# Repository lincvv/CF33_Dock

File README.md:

# CF33_Dock
**Detect Bypass Station for Panasonic CF33 with 4 USB Ports**

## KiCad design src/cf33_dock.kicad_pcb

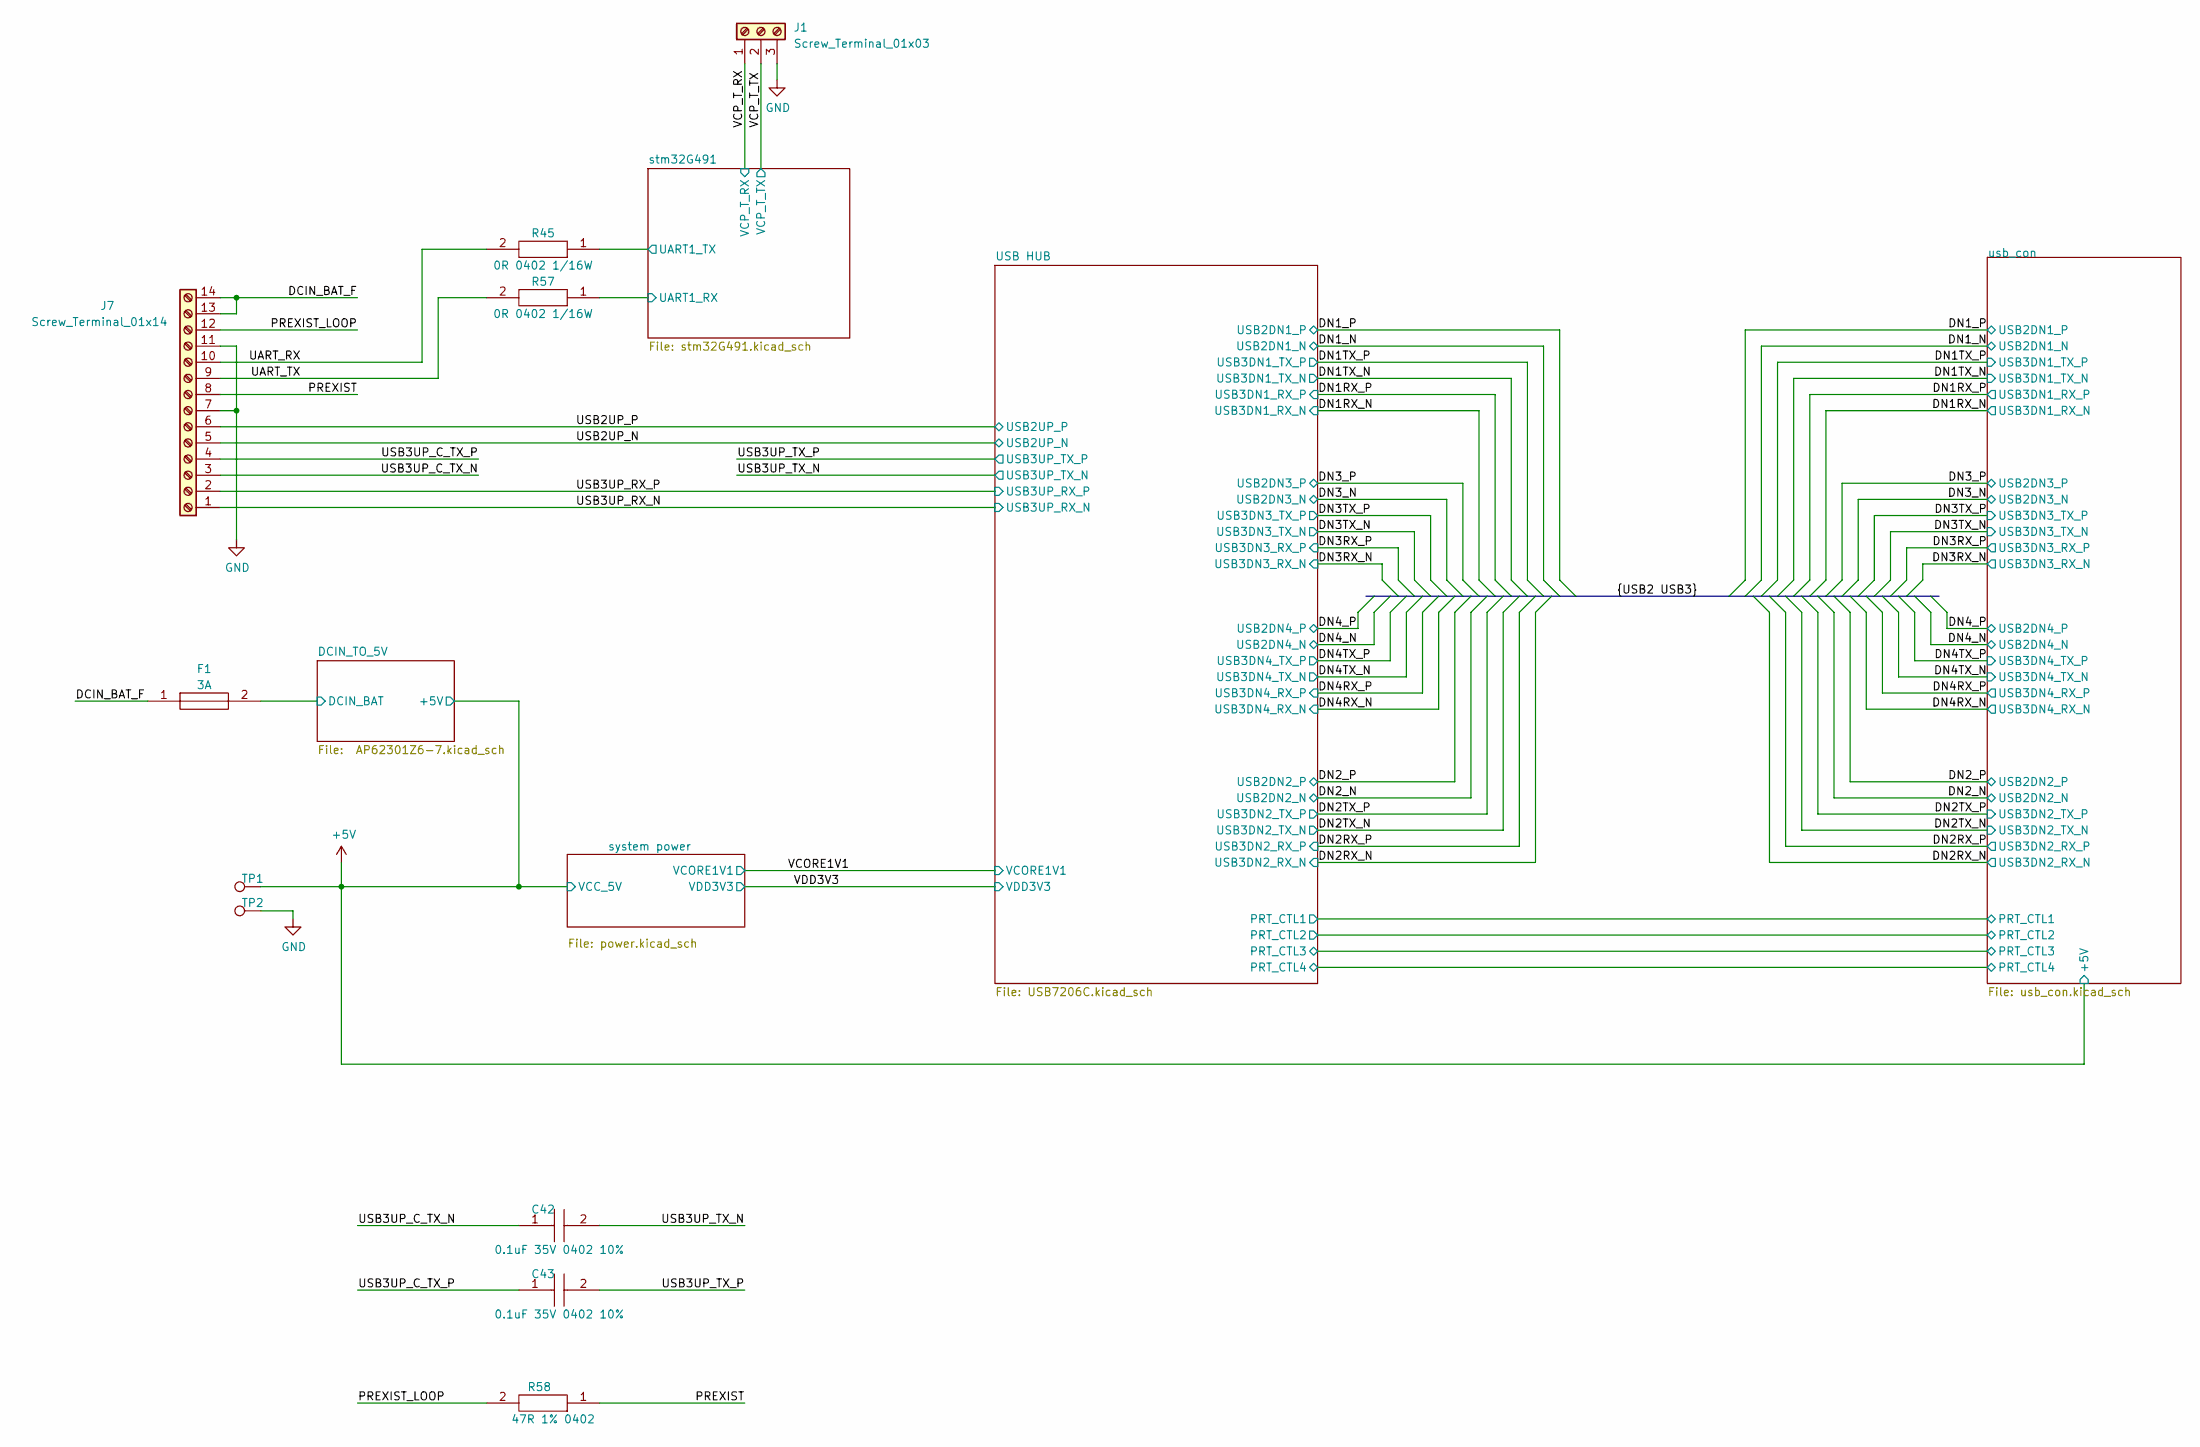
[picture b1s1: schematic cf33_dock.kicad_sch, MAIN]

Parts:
C42, C43: 0.1uF 35V 0402 10%; C_0402_1005Metric; Manufacturer_Part_Number CGA2B3X7R1V104K050BB; Mouser Part Number 810-CGA2B3X7R1V104K
F1: 3A; SF1206F300M2; Manufacturer_Part_Number SF-1206F300M-2
J1: Screw_Terminal_01x03; PinHeader_1x03_P2.54mm_Vertical
J7: Screw_Terminal_01x14; PinHeader_1x14_P2.54mm_Vertical
R45, R57: 0R 0402 1/16W; R_0402_1005Metric; Manufacturer_Part_Number CRCW04020000ZSTD; Mouser Part Number 71-CRCW0402-0
R58: 47R 1% 0402; R_0402_1005Metric; Manufacturer_Part_Number CR0402-FX-47R0GLF
TP1, TP2: TestPoint; TestPoint_THTPad_D2.0mm_Drill1.0mm

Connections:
+5V: TP1.1; also elsewhere on the board
/DCIN_BAT_F: F1.1, J7.13, J7.14
/PREXIST: J7.8, R58.1
/PREXIST_LOOP: J7.12, R58.2
/UART_RX: J7.10, R45.2
/UART_TX: J7.9, R57.2
/USB2UP_N: J7.5; also elsewhere on the board
/USB2UP_P: J7.6; also elsewhere on the board
/USB3UP_C_TX_N: C42.1, J7.3
/USB3UP_C_TX_P: C43.1, J7.4
/USB3UP_RX_N: J7.1; also elsewhere on the board
/USB3UP_RX_P: J7.2; also elsewhere on the board
/USB3UP_TX_N: C42.2; also elsewhere on the board
/USB3UP_TX_P: C43.2; also elsewhere on the board
/VCP_T_RX: J1.1; also elsewhere on the board
/VCP_T_TX: J1.2; also elsewhere on the board
/stm32G491/UART1_RX: R57.1; also elsewhere on the board
/stm32G491/UART1_TX: R45.1; also elsewhere on the board
DCIN_BAT: F1.2; also elsewhere on the board
GND: J1.3, J7.7, J7.11, TP2.1; also elsewhere on the board

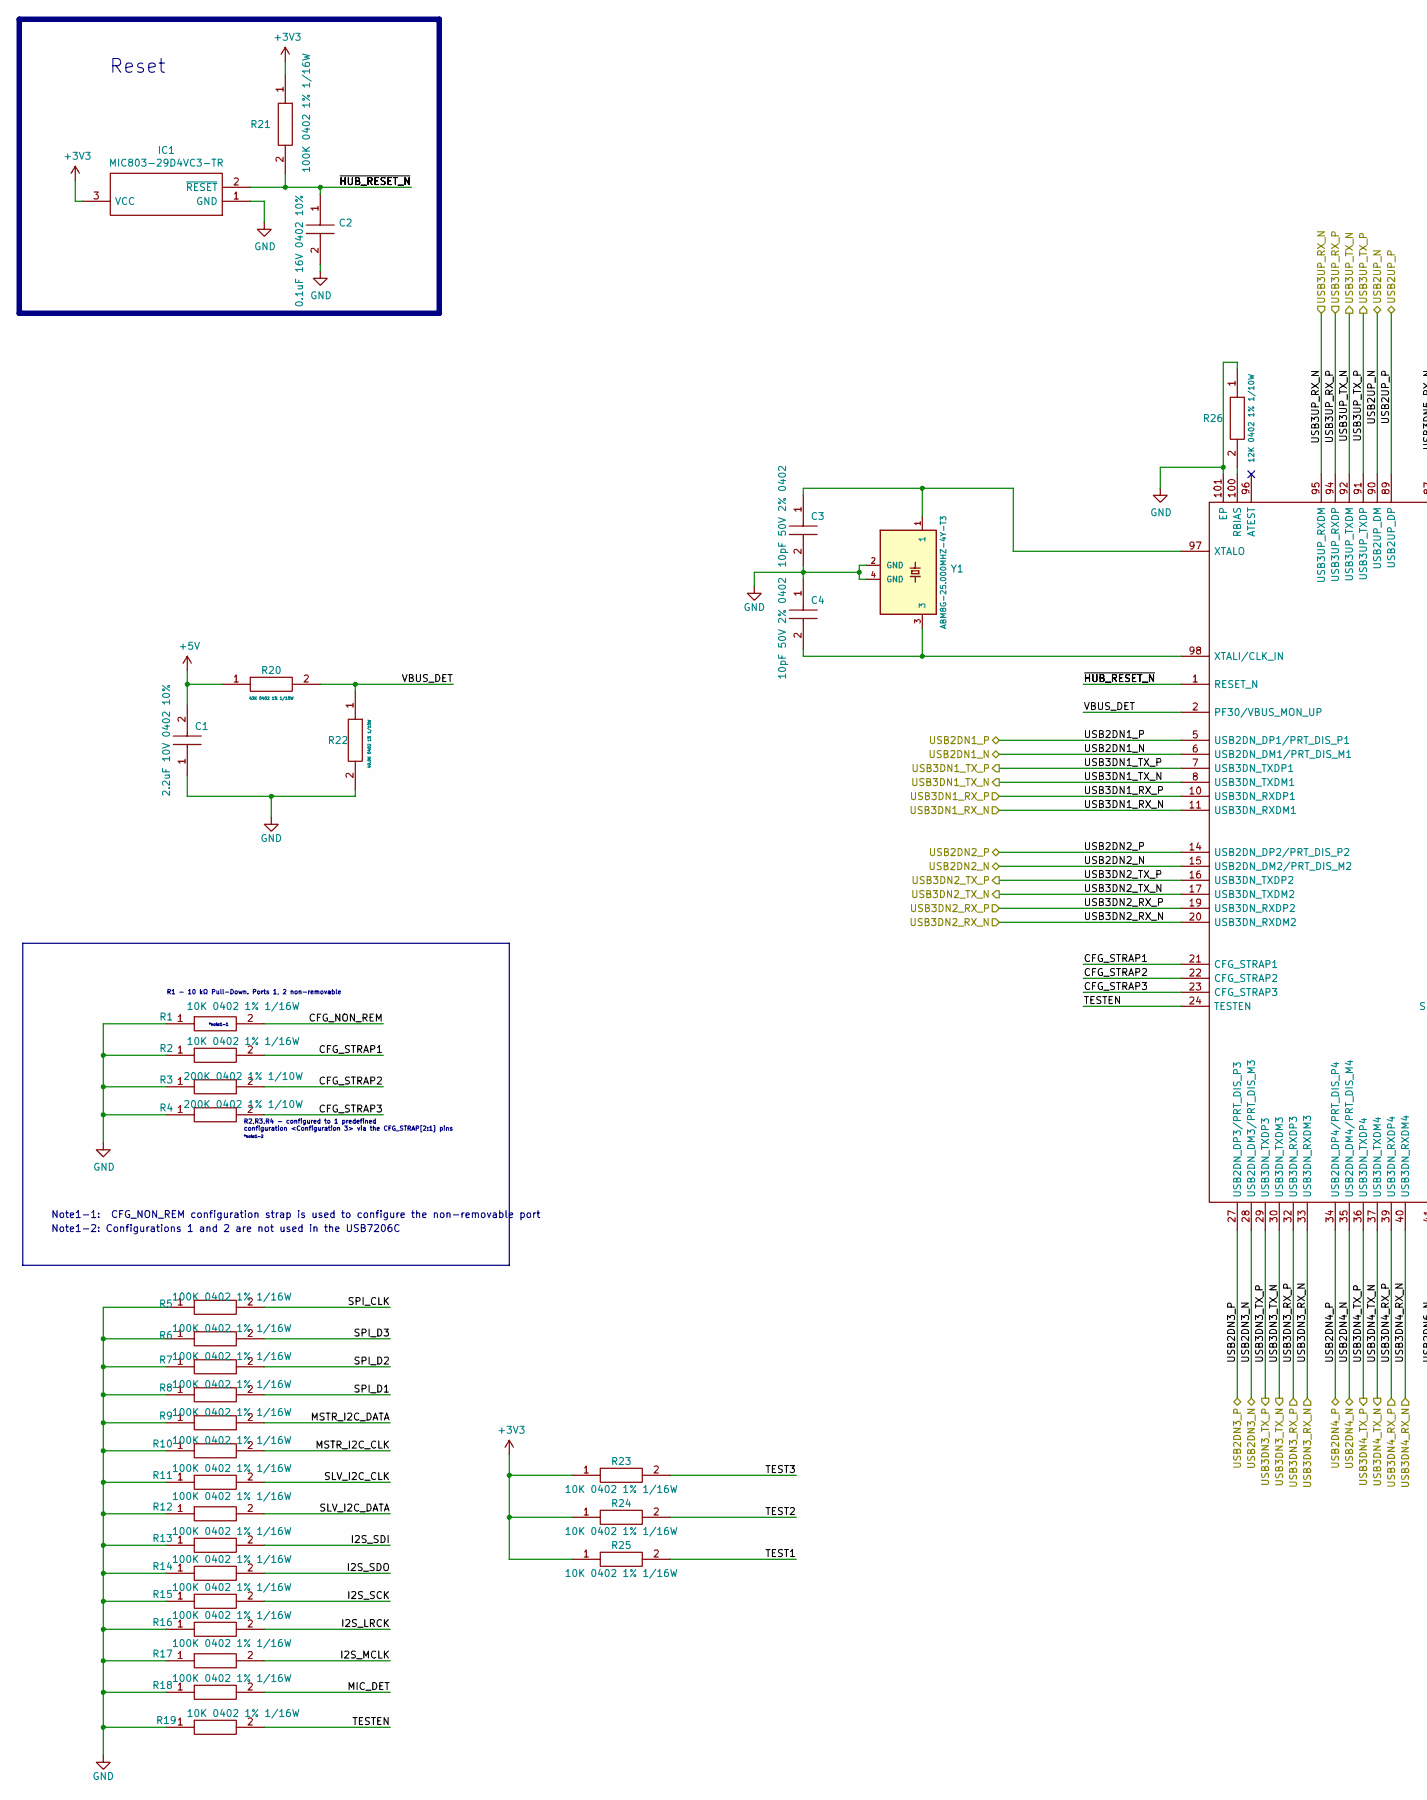
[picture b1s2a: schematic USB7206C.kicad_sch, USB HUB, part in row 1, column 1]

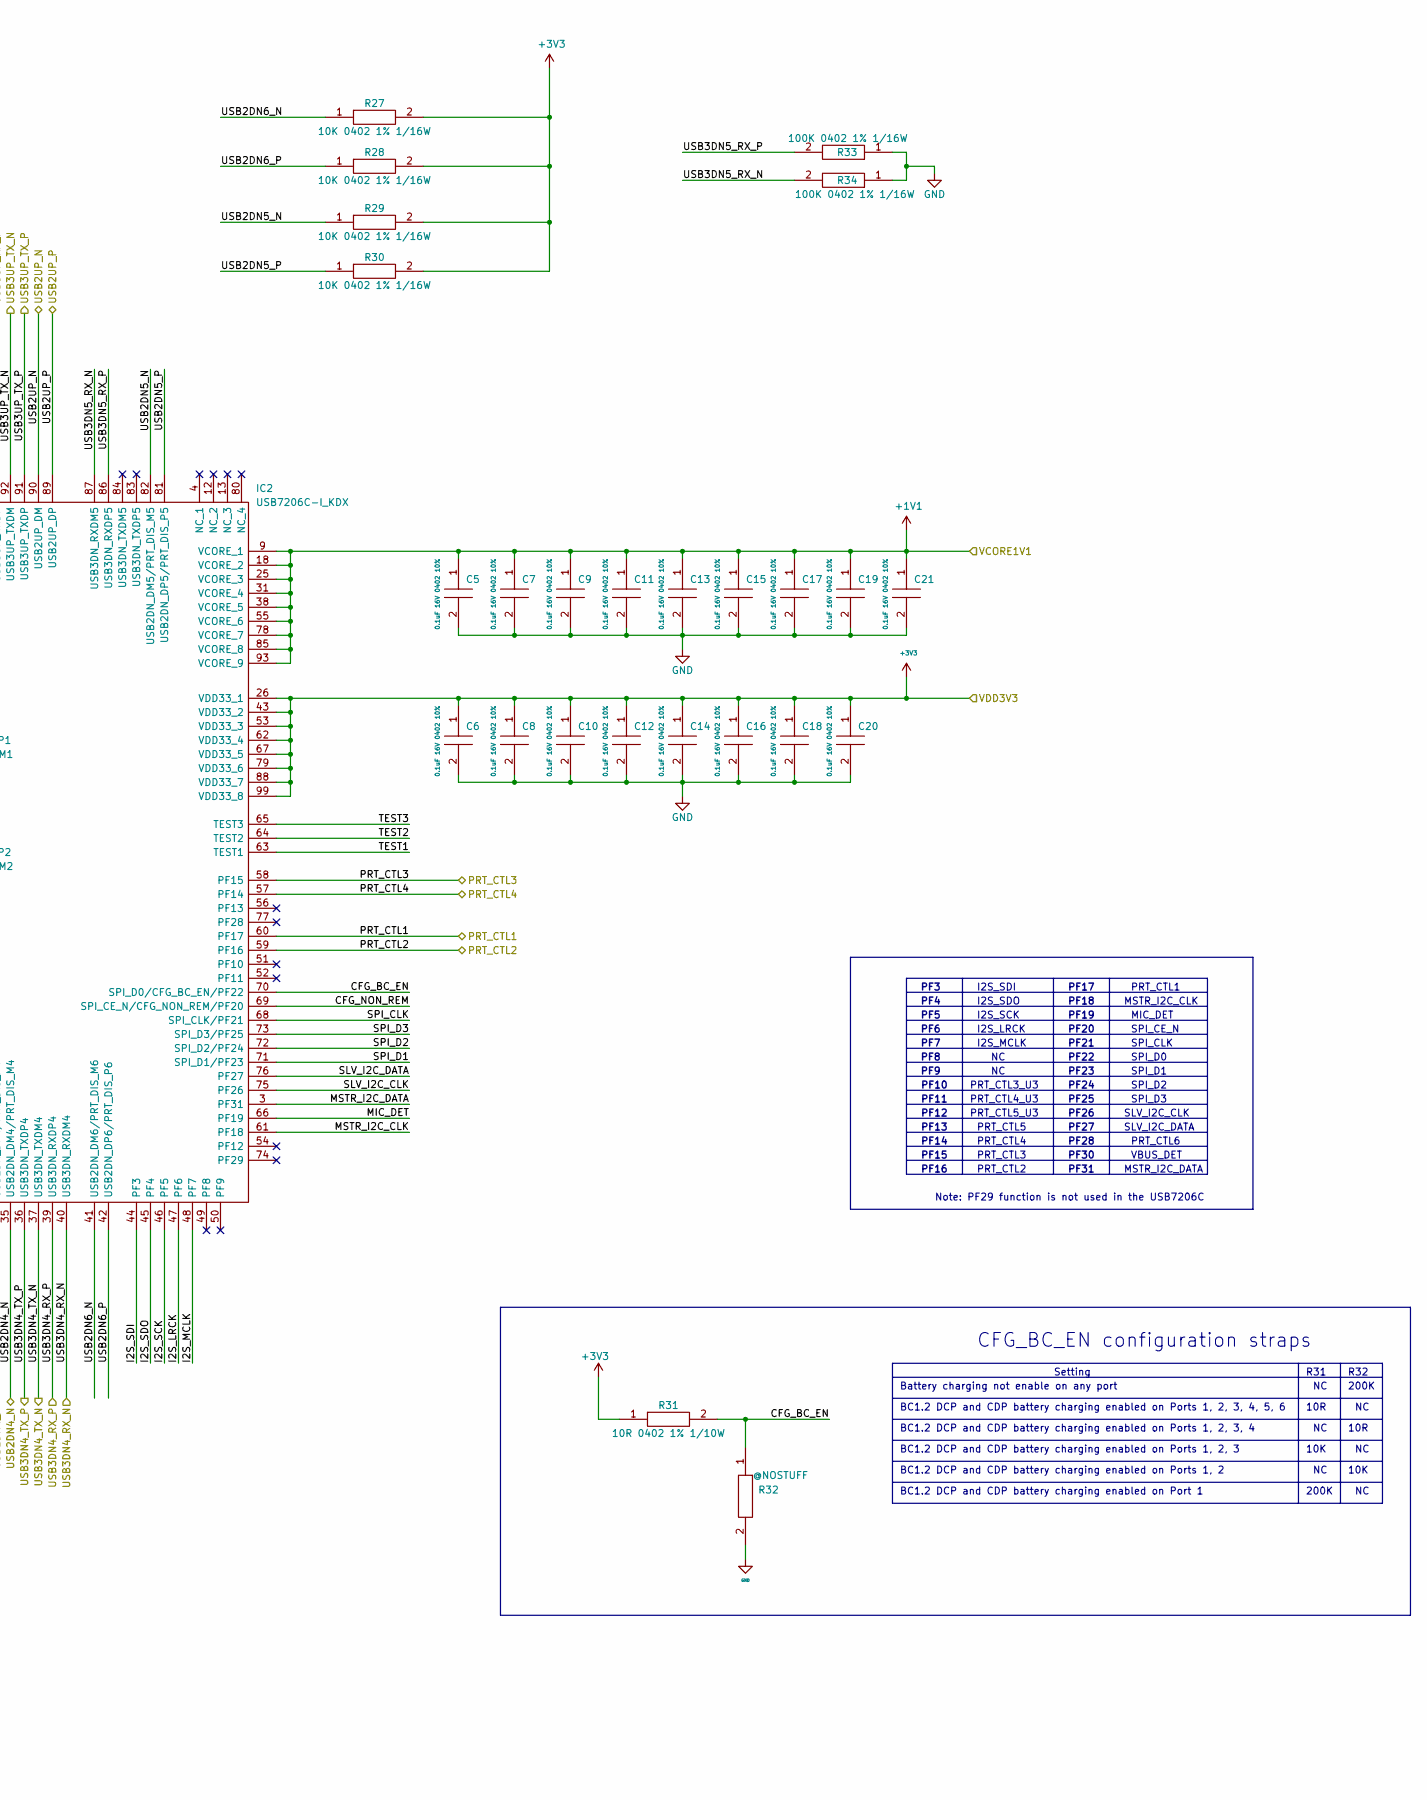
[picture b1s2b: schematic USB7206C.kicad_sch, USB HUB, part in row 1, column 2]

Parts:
C1: 2.2uF 10V 0402 10%; C_0402_1005Metric; Manufacturer_Part_Number GRM155C71A225KE11D; Mouser Part Number 81-GRM155C71A225KE1D
C2, C5, C6, C7, C8, C9, C10, C11, C12, C13, C14, C15, C16, C17, C18, C19, C20, C21: 0.1uF 16V 0402 10%; C_0402_1005Metric; Manufacturer_Part_Number GRM155R71C104KA88D; Mouser Part Number N/A
C3, C4: 10pF 50V 2% 0402; C_0402_1005Metric; Manufacturer_Part_Number GJM1555C1H100GB01D; Mouser Part Number 81-GJM1555C1H100GB01
IC1: MIC803-29D4VC3-TR; SOT65P210X100-3N; Manufacturer_Part_Number MIC803-29D4VC3-TR; Mouser Part Number 998-MIC803-29D4VC3TR
IC2: USB7206C-I_KDX; QFN40P1200X1200X90-101N-D; Mouser Part Number 579-USB7206C-I/KDX
R1, R2, R19, R23, R24, R25, R27, R28, R29, R30: 10K 0402 1% 1/16W; R_0402_1005Metric; Manufacturer_Part_Number AC0402FR-0710KL; Mouser Part Number 603-AC0402FR-0710KL
R3, R4: 200K 0402 1% 1/10W; R_0402_1005Metric; Manufacturer_Part_Number ERJ-U02F2003X
R5, R6, R7, R8, R9, R10, R11, R12, R13, R14, R15, R16, R17, R18, R21, R33, R34: 100K 0402 1% 1/16W; R_0402_1005Metric; Manufacturer_Part_Number SFR01MZPF1003; Mouser Part Number 755-SFR01MZPF1003
R20: 43K 0402 1% 1/10W; R_0402_1005Metric; Manufacturer_Part_Number ERJ-U02F4302X; Mouser Part Number 667-ERJ-U02F4302X
R22: 49.9K 0402 1% 1/10W; R_0402_1005Metric; Manufacturer_Part_Number ERJ-U02F4992X; Mouser Part Number 667-ERJ-U02F4992X
R26: 12K 0402 1% 1/10W; R_0402_1005Metric; Manufacturer_Part_Number ERJ-U02F1202X
R31, R32: 10R 0402 1% 1/10W; R_0402_1005Metric; Manufacturer_Part_Number ERJ-2RKF10R0X; Mouser Part Number 667-ERJ-2RKF10R0X
Y1: ABM8G-25.000MHZ-4Y-T3; ABM8G48000MHZ18D2YT; Manufacturer_Part_Number ABM8G-25.000MHZ-4Y-T3; Mouser Part Number 815-ABM8G-25-4YT3

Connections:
+1V1: C5.1, C7.1, C9.1, C11.1, C13.1, C15.1, C17.1, C19.1, C21.1, IC2.9 (VCORE_1), IC2.18 (VCORE_2), IC2.25 (VCORE_3), IC2.31 (VCORE_4), IC2.38 (VCORE_5), IC2.55 (VCORE_6), IC2.78 (VCORE_7), IC2.85 (VCORE_8), IC2.93 (VCORE_9); also elsewhere on the board
+3V3: C6.1, C8.1, C10.1, C12.1, C14.1, C16.1, C18.1, C20.1, IC1.3 (VCC), IC2.26 (VDD33_1), IC2.43 (VDD33_2), IC2.53 (VDD33_3), IC2.62 (VDD33_4), IC2.67 (VDD33_5), IC2.79 (VDD33_6), IC2.88 (VDD33_7), IC2.99 (VDD33_8), R21.1, R23.1, R24.1, R25.1, R27.2, R28.2, R29.2, R30.2, R31.1; also elsewhere on the board
+5V: C1.2, R20.1; also elsewhere on the board
/DN1RX_N: IC2.11 (USB3DN_RXDM1); also elsewhere on the board
/DN1RX_P: IC2.10 (USB3DN_RXDP1); also elsewhere on the board
/DN1TX_N: IC2.8 (USB3DN_TXDM1); also elsewhere on the board
/DN1TX_P: IC2.7 (USB3DN_TXDP1); also elsewhere on the board
/DN1_N: IC2.6 (USB2DN_DM1/PRT_DIS_M1); also elsewhere on the board
/DN1_P: IC2.5 (USB2DN_DP1/PRT_DIS_P1); also elsewhere on the board
/DN2RX_N: IC2.20 (USB3DN_RXDM2); also elsewhere on the board
/DN2RX_P: IC2.19 (USB3DN_RXDP2); also elsewhere on the board
/DN2TX_N: IC2.17 (USB3DN_TXDM2); also elsewhere on the board
/DN2TX_P: IC2.16 (USB3DN_TXDP2); also elsewhere on the board
/DN2_N: IC2.15 (USB2DN_DM2/PRT_DIS_M2); also elsewhere on the board
/DN2_P: IC2.14 (USB2DN_DP2/PRT_DIS_P2); also elsewhere on the board
/DN3RX_N: IC2.33 (USB3DN_RXDM3); also elsewhere on the board
/DN3RX_P: IC2.32 (USB3DN_RXDP3); also elsewhere on the board
/DN3TX_N: IC2.30 (USB3DN_TXDM3); also elsewhere on the board
/DN3TX_P: IC2.29 (USB3DN_TXDP3); also elsewhere on the board
/DN3_N: IC2.28 (USB2DN_DM3/PRT_DIS_M3); also elsewhere on the board
/DN3_P: IC2.27 (USB2DN_DP3/PRT_DIS_P3); also elsewhere on the board
/DN4RX_N: IC2.40 (USB3DN_RXDM4); also elsewhere on the board
/DN4RX_P: IC2.39 (USB3DN_RXDP4); also elsewhere on the board
/DN4TX_N: IC2.37 (USB3DN_TXDM4); also elsewhere on the board
/DN4TX_P: IC2.36 (USB3DN_TXDP4); also elsewhere on the board
/DN4_N: IC2.35 (USB2DN_DM4/PRT_DIS_M4); also elsewhere on the board
/DN4_P: IC2.34 (USB2DN_DP4/PRT_DIS_P4); also elsewhere on the board
/USB2UP_N: IC2.90 (USB2UP_DM); also elsewhere on the board
/USB2UP_P: IC2.89 (USB2UP_DP); also elsewhere on the board
/USB3UP_RX_N: IC2.95 (USB3UP_RXDM); also elsewhere on the board
/USB3UP_RX_P: IC2.94 (USB3UP_RXDP); also elsewhere on the board
/USB3UP_TX_N: IC2.92 (USB3UP_TXDM); also elsewhere on the board
/USB3UP_TX_P: IC2.91 (USB3UP_TXDP); also elsewhere on the board
/USB HUB/CFG_BC_EN: IC2.70 (SPI_D0/CFG_BC_EN/PF22), R31.2, R32.1
/USB HUB/CFG_NON_REM: IC2.69 (SPI_CE_N/CFG_NON_REM/PF20), R1.2
/USB HUB/CFG_STRAP1: IC2.21 (CFG_STRAP1), R2.2
/USB HUB/CFG_STRAP2: IC2.22 (CFG_STRAP2), R3.2
/USB HUB/CFG_STRAP3: IC2.23 (CFG_STRAP3), R4.2
/USB HUB/HUB_RESET_N: C2.1, IC1.2 (~RESET), IC2.1 (RESET_N), R21.2
/USB HUB/I2S_LRCK: IC2.47 (PF6), R16.2
/USB HUB/I2S_MCLK: IC2.48 (PF7), R17.2
/USB HUB/I2S_SCK: IC2.46 (PF5), R15.2
/USB HUB/I2S_SDI: IC2.44 (PF3), R13.2
/USB HUB/I2S_SDO: IC2.45 (PF4), R14.2
/USB HUB/MIC_DET: IC2.66 (PF19), R18.2
/USB HUB/MSTR_I2C_CLK: IC2.61 (PF18), R10.2
/USB HUB/MSTR_I2C_DATA: IC2.3 (PF31), R9.2
/USB HUB/PRT_CTL1: IC2.60 (PF17); also elsewhere on the board
/USB HUB/PRT_CTL2: IC2.59 (PF16); also elsewhere on the board
/USB HUB/PRT_CTL3: IC2.58 (PF15); also elsewhere on the board
/USB HUB/PRT_CTL4: IC2.57 (PF14); also elsewhere on the board
/USB HUB/SLV_I2C_CLK: IC2.75 (PF26), R11.2
/USB HUB/SLV_I2C_DATA: IC2.76 (PF27), R12.2
/USB HUB/SPI_CLK: IC2.68 (SPI_CLK/PF21), R5.2
/USB HUB/SPI_D1: IC2.71 (SPI_D1/PF23), R8.2
/USB HUB/SPI_D2: IC2.72 (SPI_D2/PF24), R7.2
/USB HUB/SPI_D3: IC2.73 (SPI_D3/PF25), R6.2
/USB HUB/TEST1: IC2.63 (TEST1), R25.2
/USB HUB/TEST2: IC2.64 (TEST2), R24.2
/USB HUB/TEST3: IC2.65 (TEST3), R23.2
/USB HUB/TESTEN: IC2.24 (TESTEN), R19.2
/USB HUB/USB2DN5_N: IC2.82 (USB2DN_DM5/PRT_DIS_M5), R29.1
/USB HUB/USB2DN5_P: IC2.81 (USB2DN_DP5/PRT_DIS_P5), R30.1
/USB HUB/USB2DN6_N: IC2.41 (USB2DN_DM6/PRT_DIS_M6), R27.1
/USB HUB/USB2DN6_P: IC2.42 (USB2DN_DP6/PRT_DIS_P6), R28.1
/USB HUB/USB3DN5_RX_N: IC2.87 (USB3DN_RXDM5), R34.2
/USB HUB/USB3DN5_RX_P: IC2.86 (USB3DN_RXDP5), R33.2
/USB HUB/VBUS_DET: IC2.2 (PF30/VBUS_MON_UP), R20.2, R22.1
GND: C1.1, C2.2, C3.2, C4.1, C5.2, C6.2, C7.2, C8.2, C9.2, C10.2, C11.2, C12.2, C13.2, C14.2, C15.2, C16.2, C17.2, C18.2, C19.2, C20.2, C21.2, IC1.1 (GND), IC2.101 (EP), R1.1, R2.1, R3.1, R4.1, R5.1, R6.1, R7.1, R8.1, R9.1, R10.1, R11.1, R12.1, R13.1, R14.1, R15.1, R16.1, R17.1, R18.1, R19.1, R22.2, R26.1, R32.2, R33.1, R34.1, Y1.2 (GND), Y1.4 (GND); also elsewhere on the board
unnamed: IC2.100 (RBIAS), R26.2
unnamed: C4.2, IC2.98 (XTALI/CLK_IN), Y1.3
unnamed: C3.1, IC2.97 (XTALO), Y1.1

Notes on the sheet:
Reset
10K
MSTR_I2C_CLK
PF17
PF4
PF8
PRT_CTL3
PF5
PF22
Setting
PF10
PRT_CTL3_U3
PF3
PF11
200K
PF13
PF27
PF28
MIC_DET
PF30
PF23
PF15
PRT_CTL6
PF24
BC1.2 DCP and CDP battery charging enabled on Port 1
PF19
PF26
SPI_CE_N
BC1.2 DCP and CDP battery charging enabled on Ports 1, 2, 3
PF20
BC1.2 DCP and CDP battery charging enabled on Ports 1, 2, 3, 4
R31
PF12
Note1-2: Configurations 1 and 2 are not used in the USB7206C
PRT_CTL5_U3
*note1-1
I2S_LRCK
SLV_I2C_CLK
SPI_CLK
Note: PF29 function is not used in the USB7206C

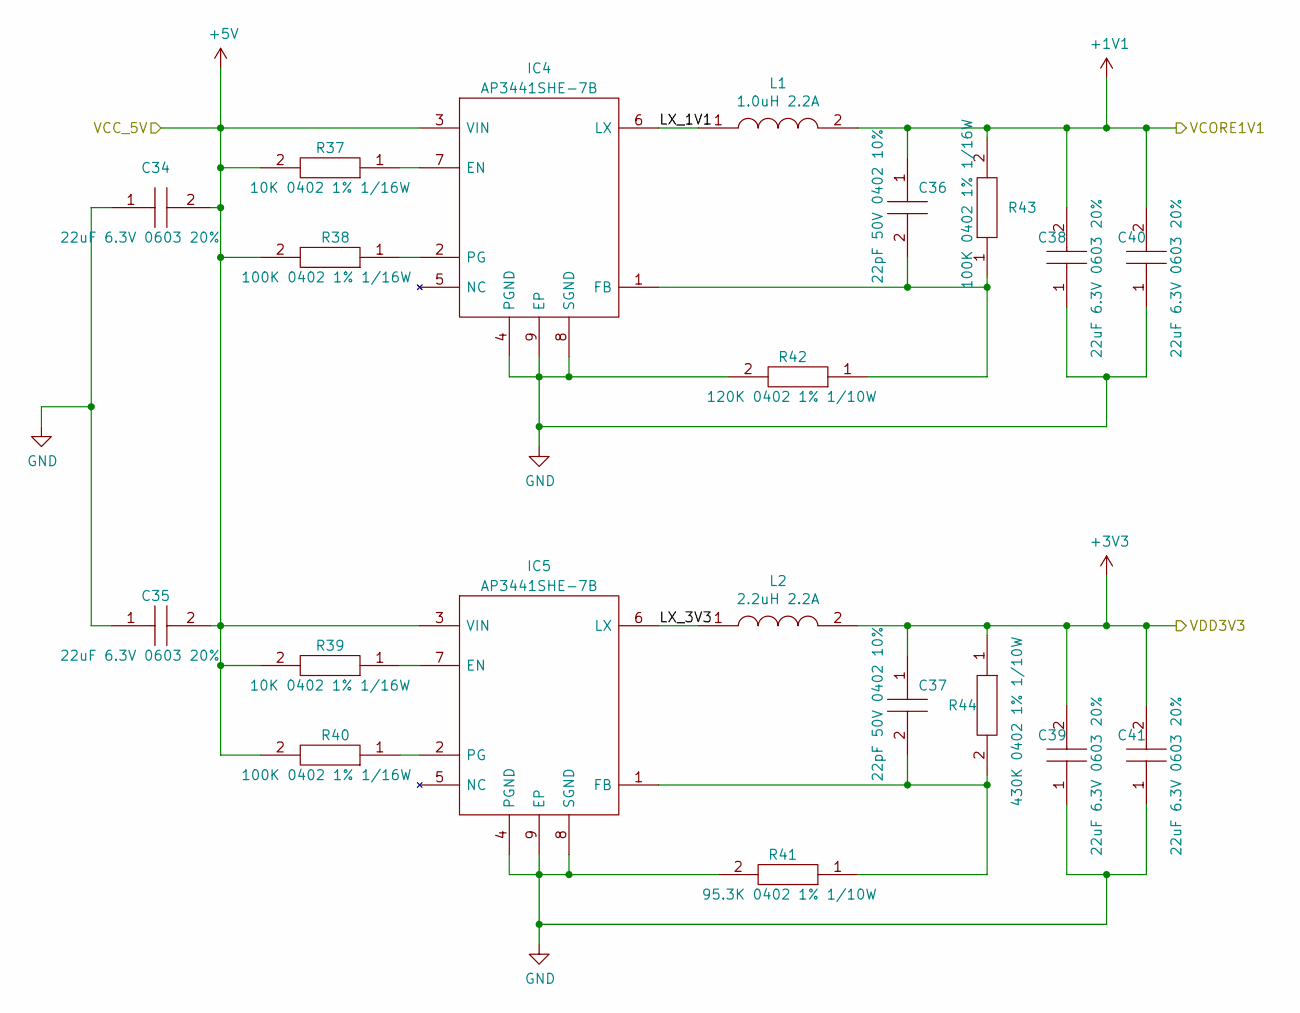
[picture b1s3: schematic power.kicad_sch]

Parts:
C34, C35, C38, C39, C40, C41: 22uF 6.3V 0603 20%; C_0603_1608Metric; Manufacturer_Part_Number GRM188R60J226MEA0D; Mouser Part Number 81-GRM188R60J226ME0D
C36, C37: 22pF 50V 0402 10%; C_0402_1005Metric; Manufacturer_Part_Number C0402C220K5RACTU; Mouser Part Number 80-C0402C220K5RACTU
IC4, IC5: AP3441SHE-7B; SON50P201X201X60-9N-D; Manufacturer_Part_Number AP3441SHE-7B; Mouser Part Number 621-AP3441SHE-7B
L1: 1.0uH 2.2A; 1285ASH1R0MP2; Manufacturer_Part_Number 1285AS-H-1R0M=P2; Mouser Part Number 81-1285AS-H-1R0MP2
L2: 2.2uH 2.2A; DFE2HCAH1R0MJ0L; Manufacturer_Part_Number 1239AS-H-2R2M=P2; Mouser Part Number 81-1239AS-H-2R2MP2
R37, R39: 10K 0402 1% 1/16W; R_0402_1005Metric; Manufacturer_Part_Number AC0402FR-0710KL; Mouser Part Number 603-AC0402FR-0710KL
R38, R40, R43: 100K 0402 1% 1/16W; R_0402_1005Metric; Manufacturer_Part_Number SFR01MZPF1003; Mouser Part Number 755-SFR01MZPF1003
R41: 95.3K 0402 1% 1/10W; R_0402_1005Metric; Manufacturer_Part_Number ERJ-U02F9532X; Mouser Part Number 667-ERJ-U02F9532X
R42: 120K 0402 1% 1/10W; R_0402_1005Metric; Manufacturer_Part_Number ERJ2RKF1203X
R44: 430K 0402 1% 1/10W; R_0402_1005Metric; Manufacturer_Part_Number ERJ-U02F4303X

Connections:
+1V1: C36.1, C38.2, C40.2, L1.2, R43.2; also elsewhere on the board
+3V3: C37.1, C39.2, C41.2, L2.2, R44.1; also elsewhere on the board
+5V: C34.2, C35.2, IC4.3 (VIN), IC5.3 (VIN), R37.2, R38.2, R39.2, R40.2; also elsewhere on the board
/system power/LX_1V1: IC4.6 (LX), L1.1
/system power/LX_3V3: IC5.6 (LX), L2.1
GND: C34.1, C35.1, C38.1, C39.1, C40.1, C41.1, IC4.4 (PGND), IC4.8 (SGND), IC4.9 (EP), IC5.4 (PGND), IC5.8 (SGND), IC5.9 (EP), R41.2, R42.2; also elsewhere on the board
unnamed: IC4.7 (EN), R37.1
unnamed: C36.2, IC4.1 (FB), R42.1, R43.1
unnamed: IC4.2 (PG), R38.1
unnamed: IC5.7 (EN), R39.1
unnamed: C37.2, IC5.1 (FB), R41.1, R44.2
unnamed: IC5.2 (PG), R40.1

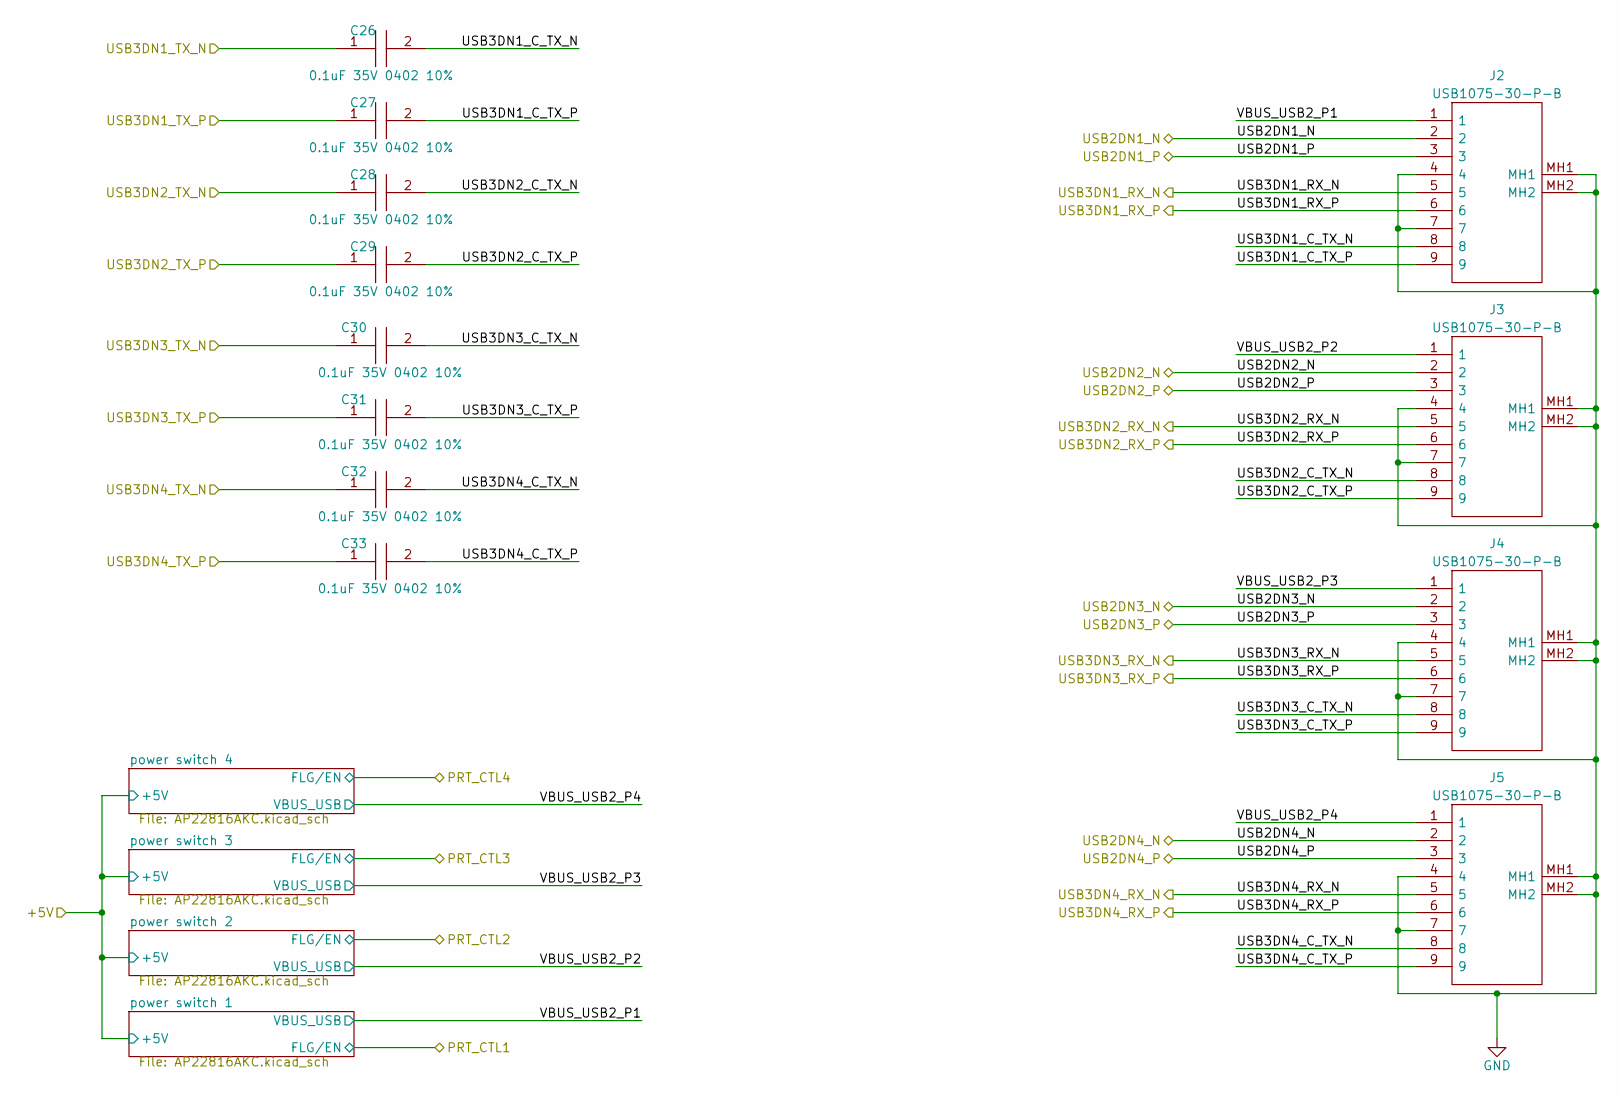
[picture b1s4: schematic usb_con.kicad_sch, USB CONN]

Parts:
C26, C27, C28, C29, C30, C31, C32, C33: 0.1uF 35V 0402 10%; C_0402_1005Metric; Manufacturer_Part_Number CGA2B3X7R1V104K050BB; Mouser Part Number 810-CGA2B3X7R1V104K
J2, J3, J4, J5: USB1075-30-P-B; USB107530PB; Manufacturer_Part_Number USB1075-30-P-B; Mouser Part Number 640-USB1075-30-P-B

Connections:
/DN1RX_N: J2.5; also elsewhere on the board
/DN1RX_P: J2.6; also elsewhere on the board
/DN1TX_N: C26.1; also elsewhere on the board
/DN1TX_P: C27.1; also elsewhere on the board
/DN1_N: J2.2; also elsewhere on the board
/DN1_P: J2.3; also elsewhere on the board
/DN2RX_N: J3.5; also elsewhere on the board
/DN2RX_P: J3.6; also elsewhere on the board
/DN2TX_N: C28.1; also elsewhere on the board
/DN2TX_P: C29.1; also elsewhere on the board
/DN2_N: J3.2; also elsewhere on the board
/DN2_P: J3.3; also elsewhere on the board
/DN3RX_N: J4.5; also elsewhere on the board
/DN3RX_P: J4.6; also elsewhere on the board
/DN3TX_N: C30.1; also elsewhere on the board
/DN3TX_P: C31.1; also elsewhere on the board
/DN3_N: J4.2; also elsewhere on the board
/DN3_P: J4.3; also elsewhere on the board
/DN4RX_N: J5.5; also elsewhere on the board
/DN4RX_P: J5.6; also elsewhere on the board
/DN4TX_N: C32.1; also elsewhere on the board
/DN4TX_P: C33.1; also elsewhere on the board
/DN4_N: J5.2; also elsewhere on the board
/DN4_P: J5.3; also elsewhere on the board
/usb_con/USB3DN1_C_TX_N: C26.2, J2.8
/usb_con/USB3DN1_C_TX_P: C27.2, J2.9
/usb_con/USB3DN2_C_TX_N: C28.2, J3.8
/usb_con/USB3DN2_C_TX_P: C29.2, J3.9
/usb_con/USB3DN3_C_TX_N: C30.2, J4.8
/usb_con/USB3DN3_C_TX_P: C31.2, J4.9
/usb_con/USB3DN4_C_TX_N: C32.2, J5.8
/usb_con/USB3DN4_C_TX_P: C33.2, J5.9
/usb_con/VBUS_USB2_P1: J2.1; also elsewhere on the board
/usb_con/VBUS_USB2_P2: J3.1; also elsewhere on the board
/usb_con/VBUS_USB2_P3: J4.1; also elsewhere on the board
/usb_con/VBUS_USB2_P4: J5.1; also elsewhere on the board
GND: J2.4, J2.7, J2.MH1, J2.MH2, J3.4, J3.7, J3.MH1, J3.MH2, J4.4, J4.7, J4.MH1, J4.MH2, J5.4, J5.7, J5.MH1, J5.MH2; also elsewhere on the board
